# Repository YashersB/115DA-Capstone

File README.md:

# 115DA-Capstone
Github respitory for Pulse Oximeter

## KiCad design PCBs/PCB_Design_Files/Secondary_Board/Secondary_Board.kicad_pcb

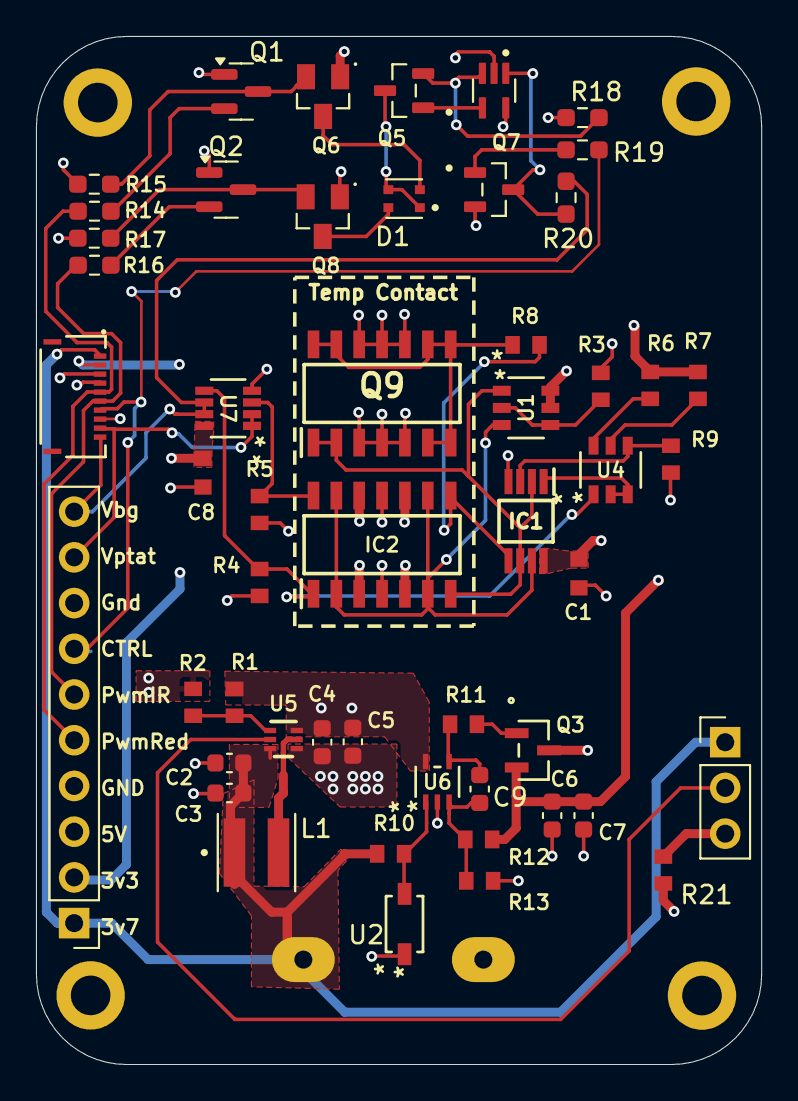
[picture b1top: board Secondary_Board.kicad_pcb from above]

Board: 4 copper layers, 40.3 x 57.1 mm, 57 parts (1 on the bottom side), 39 nets.

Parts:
BT2: Battery_Cell; bat_pads
C1, C8: .1u; 0603_capacitor
C2, C3, C6, C7: 4.7u; C_0603_1608Metric
C4, C5: 22u; C_0603_1608Metric
C9: 180p; C_0603_1608Metric
D1: VSMD66694; DIO_VSMD66694
H1, H2, H3, H4: MountingHole_Pad; MountingHole_2.2mm_M2_DIN965_Pad
IC1: TLV2333IDGKR
IC2: 320S14-U; That320_pnp
J1: 5034801000; Conn_FFC_10pin
J2: Conn_01x03_Pin; PinHeader_1x03_P2.54mm_Vertical
J4: Conn_01x10_Pin; PinHeader_1x10_P2.54mm_Vertical
L1: VSEB0430H-1R0MC; IND_VSEB0430H-1R0MC
Q1, Q2: MMBT3904; SOT-23
Q3: MMBT3904; SOT23_FAS
Q5, Q7: 2N7002
Q6, Q8: BSS84
Q9: 300S14-U; That300_npn
R1: 732k; 0603_resistor
R2, R21: 100k; 0603_resistor
R3: 40k; 0603_resistor
R4: 2.2k; 0603_resistor
R5: 5k; 0603_resistor
R6, R7: 1k; 0603_resistor
R8: 105; 0603_resistor
R9: 2050; 0603_resistor
R10: 250; 0603_resistor
R11: 100; 0603_resistor
R12: 3.96k; 0603_resistor
R13: 10k; 0603_resistor
R14, R19: 1k; R_0603_1608Metric_Pad0.98x0.95mm_HandSolder
R15, R17, R20: 10k; R_0603_1608Metric_Pad0.98x0.95mm_HandSolder
R16: R; R_0603_1608Metric_Pad0.98x0.95mm_HandSolder
R18: 60; R_0603_1608Metric_Pad0.98x0.95mm_HandSolder
U1, U4: DMMT5401-7-F; DMMT5401_Dual_PNP
U2: MMSZ5221BT1G; SOD-123_ONS
U5: TPS61023DRLR; DRL0006A
U6: TLV9101IDCKR; SC70-5_DCK_TEX
U7: TLV9002
U8: OPA333AIDCKR; OPA333

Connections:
+3.7V: BT2.1 (+), C2.1, C3.1, J1.1, J2.1, J4.1, L1.1, R10.1, U5.3 (VIN)
+3V3: C1.2, C6.1, C7.1, C8.2, IC1.8 (V+), IC2.3 (E1), IC2.5 (E3), IC2.10 (E4), IC2.12 (E2), J1.2, J4.2, Q3.2 (E), R6.1, R7.1, R12.2, U1.5 (E2), U1.6 (E1), U7.8 (V+)
+5V: C4.1, C5.1, J1.3, J4.3, Q3.3 (C), Q6.1 (G), Q8.1 (G), R1.1, R15.2, R17.2, U5.6 (VOUT), U6.5 (V+), U8.5 (V+)
/LED_Driver/Current Sink: D1.1, D1.3, Q5.3
/OP_CTRL: J1.7, J4.7, R19.2
/PTAT_Bandgap/Pnp_In+: IC1.5 (+IN_B), IC2.8 (C4), R8.1
/PTAT_Bandgap/Pnp_In-: IC1.2 (-IN_A), IC1.6 (-IN_B), IC2.7 (C3), Q9.1 (C1), Q9.2 (B1), U1.1 (C1)
/PTAT_Bandgap/Pnp_base: IC1.7 (OUT_B), IC2.2 (B1), IC2.6 (B3), IC2.9 (B4), IC2.13 (B2), U1.3 (B2)
/PTAT_Bandgap/Vbg: IC2.1 (C1), R4.1, U4.1 (C1), U7.5 (IN2+)
/PTAT_Bandgap/Vptat: IC2.14 (C2), R5.1, U7.3 (IN1+)
/PWM_IR: J1.6, J4.6, R16.1
/PWM_Red: J1.5, J4.5, R14.1
/Power Management/Vfb: R1.2, R2.1, U5.1 (FB)
/V_bandgap: J1.10, J4.10, R20.1, U7.6 (IN2-), U7.7 (OUT2)
/V_ptat: J1.9, J4.9, U7.1 (OUT1), U7.2 (IN1-)
GND: BT2.2 (-), C1.1, C2.2, C3.2, C4.2, C5.2, C6.2, C7.2, C8.1, H1.1, H2.1, H3.1, H4.1, IC1.4 (V-), IC2.4 (NC_1), IC2.11 (NC_2), J1.4, J1.8, J4.4, J4.8, Q1.1 (E), Q2.1 (E), Q7.2, Q9.3 (E1), Q9.4 (SUB_1), Q9.5 (E3), Q9.10 (E4), Q9.11 (SUB_2), Q9.12 (E2), R2.2, R3.2, R4.2, R5.2, R9.2, R13.1, R18.1, R21.2, U2.1 (CATHODE), U5.4 (GND), U6.2 (V-), U7.4 (V-), U8.2 (V-)
unnamed: IC1.3 (+IN_A), R9.1, U4.4 (C2)
unnamed: IC1.1 (OUT_A), U4.2 (B1), U4.3 (B2)
unnamed: J2.2, U5.2 (EN)
unnamed: J2.3, R21.1
unnamed: Q1.2 (B), R14.2
unnamed: Q1.3 (C), Q6.2 (S), R15.1
unnamed: Q2.2 (B), R16.2
unnamed: Q2.3 (C), Q8.2 (S), R17.1
unnamed: Q3.1 (B), R11.2
unnamed: D1.2, Q6.3 (D)
unnamed: Q7.1, R19.1
unnamed: D1.4, Q8.3 (D)
unnamed: Q9.6 (B3), Q9.7 (C3), Q9.8 (C4), Q9.9 (B4), Q9.13 (B2), Q9.14 (C2), R8.2
unnamed: R3.1, U1.2 (B1), U1.4 (C2)
unnamed: R10.2, U2.2 (ANODE), U6.1 (IN+)
unnamed: R6.2, U4.6 (E1)
unnamed: R7.2, U4.5 (E2)
unnamed: L1.2, U5.5 (SW)
unnamed: C9.2, R12.1, R13.2, U6.3 (IN-)
unnamed: C9.1, R11.1, U6.4 (OUT)
unnamed: Q7.3, R20.2, U8.1 (+IN)
unnamed: Q5.2, R18.2, U8.3 (-IN)
unnamed: Q5.1, U8.4 (OUT)

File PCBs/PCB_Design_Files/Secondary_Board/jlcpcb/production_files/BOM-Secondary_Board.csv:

Comment,Designator,Footprint,LCSC,Quantity
.1u,"C1,C8",0603_capacitor,C14663,2
100,R11,0603_resistor,C22775,1
100k,R2,0603_resistor,C25803,1
10k,"R13,R15,R17,R20",0603_resistor,C25804,4
1k,"R14,R19,R6,R7",R_0603_1608Metric_Pad0.98x0.95mm_HandSolder,C21190,4
2.2k,R4,0603_resistor,C4190,1
22u,"C4,C5",C_0603_1608Metric,C59461,2
2N7002,"Q5,Q7",2N7002,C8545,2
4.7u,"C2,C3,C6,C7",C_0603_1608Metric,C19666,4
5034801000,J1,Conn_FFC_10pin,C127355,1
MMBT3904,"Q1,Q2,Q3",SOT-23,C20526,3
TLV2333IDGKR,IC1,TLV2333IDGKR,C527573,1
VSMD66694,D1,DIO_VSMD66694,C511435,1
OPA333AIDCKR,U8,OPA333,,1
DMMT5401-7-F,U4,DMMT5401_Dual_PNP,,1
MMSZ5221BT1G,U2,SOD-123_ONS,,1
BSS84,Q6,BSS84,,1
250,R10,0603_resistor,,1
60,R18,R_0603_1608Metric_Pad0.98x0.95mm_HandSolder,,1
320S14-U,IC2,That320_pnp,,1
105,R8,0603_resistor,,1
3.96k,R12,0603_resistor,,1
VSEB0430H-1R0MC,L1,IND_VSEB0430H-1R0MC,,1
Conn_01x10_Pin,J4,PinHeader_1x10_P2.54mm_Vertical,,1
TPS61023DRLR,U5,DRL0006A,,1
180p,C9,C_0603_1608Metric,,1
732k,R1,0603_resistor,,1
5k,R5,0603_resistor,,1
TLV9002,U7,TLV9002,,1
300S14-U,Q9,That300_npn,,1
2050,R9,0603_resistor,,1
BSS84,Q8,BSS84,,1
40k,R3,0603_resistor,,1
TLV9101IDCKR,U6,SC70-5_DCK_TEX,,1
R,R16,R_0603_1608Metric_Pad0.98x0.95mm_HandSolder,,1
DMMT5401-7-F,U1,DMMT5401_Dual_PNP,,1
Battery_Cell,BT2,bat_pads,,1
100k,R21,0603_resistor,,1
Conn_01x03_Pin,J2,PinHeader_1x03_P2.54mm_Vertical,,1

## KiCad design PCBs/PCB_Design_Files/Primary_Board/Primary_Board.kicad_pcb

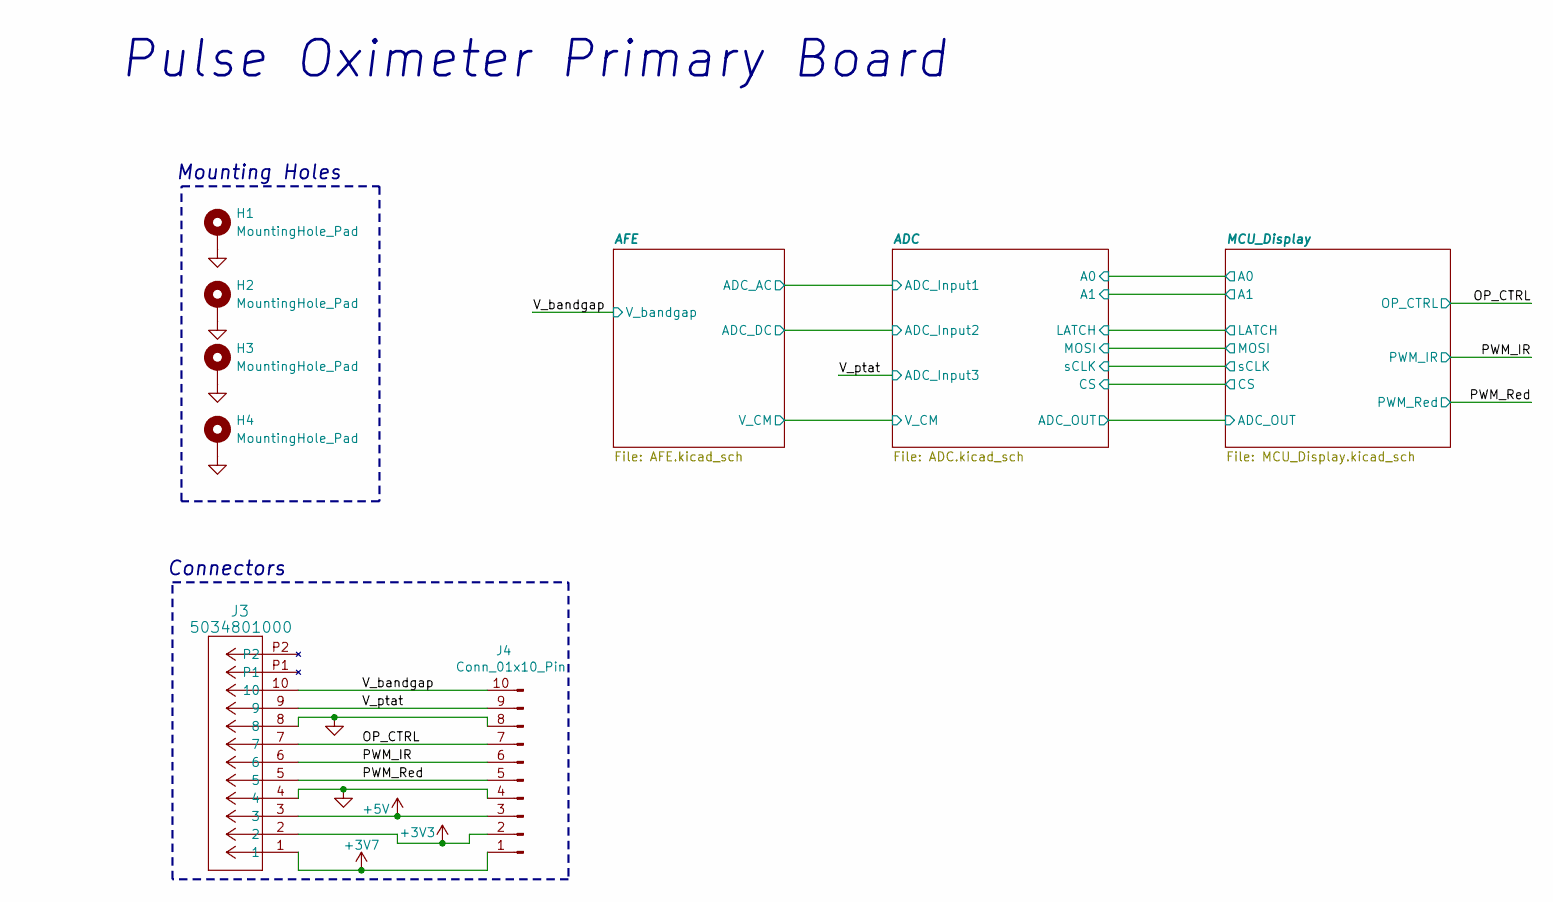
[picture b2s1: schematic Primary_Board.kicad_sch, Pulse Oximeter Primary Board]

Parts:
H1, H2, H3, H4: MountingHole_Pad; MountingHole_2.2mm_M2_DIN965_Pad
J3: 5034801000; Conn_FFC_10pin
J4: Conn_01x10_Pin; PinHeader_1x10_P2.54mm_Vertical

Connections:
+3V3: J3.2, J4.2; also elsewhere on the board
+3V7: J3.1, J4.1; also elsewhere on the board
+5V: J3.3, J4.3; also elsewhere on the board
/OP_CTRL: J3.7, J4.7; also elsewhere on the board
/PWM_IR: J3.6, J4.6; also elsewhere on the board
/PWM_Red: J3.5, J4.5; also elsewhere on the board
/V_bandgap: J3.10, J4.10; also elsewhere on the board
/V_ptat: J3.9, J4.9; also elsewhere on the board
GND: H1.1, H2.1, H3.1, H4.1, J3.4, J3.8, J4.4, J4.8; also elsewhere on the board

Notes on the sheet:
Mounting Holes
Pulse Oximeter Primary Board
Connectors

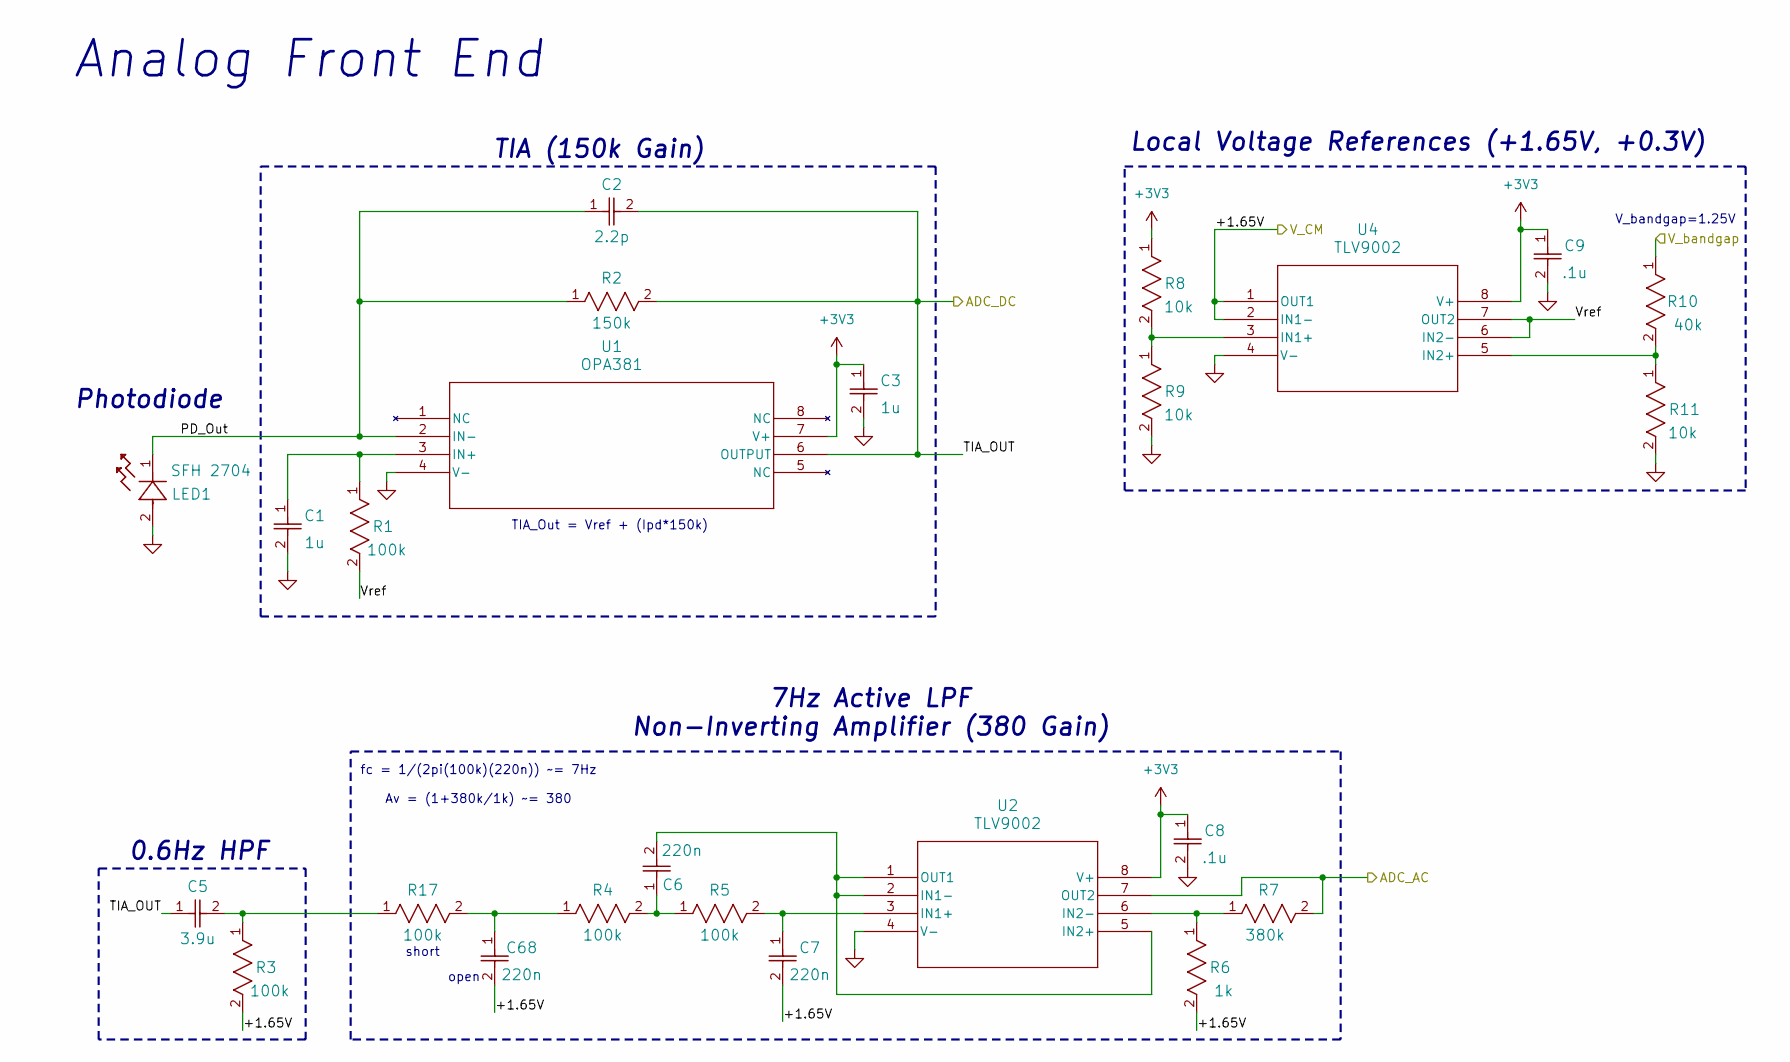
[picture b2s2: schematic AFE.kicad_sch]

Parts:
C1, C3: 1u; 0603_capacitor
C2: 2.2p; 0603_capacitor
C5: 3.9u; 0603_capacitor
C6, C7, C68: 220n; 0603_capacitor
C8, C9: .1u; 0603_capacitor
LED1: SFH 2704; SFH2704_LED
R1, R3, R4, R5, R17: 100k; 0603_resistor
R2: 150k; 0603_resistor
R6: 1k; 0603_resistor
R7: 380k; 0603_resistor
R8, R9, R11: 10k; 0603_resistor
R10: 40k; 0603_resistor
U1: OPA381
U2, U4: TLV9002

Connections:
+3V3: C3.1, C8.1, C9.1, R8.1, U1.7 (V+), U2.8 (V+), U4.8 (V+); also elsewhere on the board
/ADC/ADC_Input1: R7.2, U2.7 (OUT2); also elsewhere on the board
/AFE/+1.65V: C7.2, C68.2, R3.2, R6.2, U4.1 (OUT1), U4.2 (IN1-); also elsewhere on the board
/AFE/PD_Out: C2.1, LED1.1, R2.1, U1.2 (IN-)
/AFE/TIA_OUT: C2.2, C5.1, R2.2, U1.6 (OUTPUT); also elsewhere on the board
/AFE/Vref: R1.2, U4.6 (IN2-), U4.7 (OUT2)
/V_bandgap: R10.1; also elsewhere on the board
GND: C1.2, C3.2, C8.2, C9.2, LED1.2, R9.2, R11.2, U1.4 (V-), U2.4 (V-), U4.4 (V-); also elsewhere on the board
unnamed: C5.2, R3.1, R17.1
unnamed: C6.1, R4.2, R5.1
unnamed: C68.1, R4.1, R17.2
unnamed: C1.1, R1.1, U1.3 (IN+)
unnamed: C7.1, R5.2, U2.3 (IN1+)
unnamed: C6.2, U2.1 (OUT1), U2.2 (IN1-), U2.5 (IN2+)
unnamed: R6.1, R7.1, U2.6 (IN2-)
unnamed: R8.2, R9.1, U4.3 (IN1+)
unnamed: R10.2, R11.1, U4.5 (IN2+)

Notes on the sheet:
V_bandgap=1.25V
Local Voltage References (+1.65V, +0.3V)
Analog Front End
TIA_Out = Vref + (Ipd*150k)
TIA (150k Gain)
Photodiode
0.6Hz HPF
short
7Hz Active LPF Non-Inverting Amplifier (380 Gain)
open
fc = 1/(2pi(100k)(220n)) ~= 7Hz Av = (1+380k/1k) ~= 380

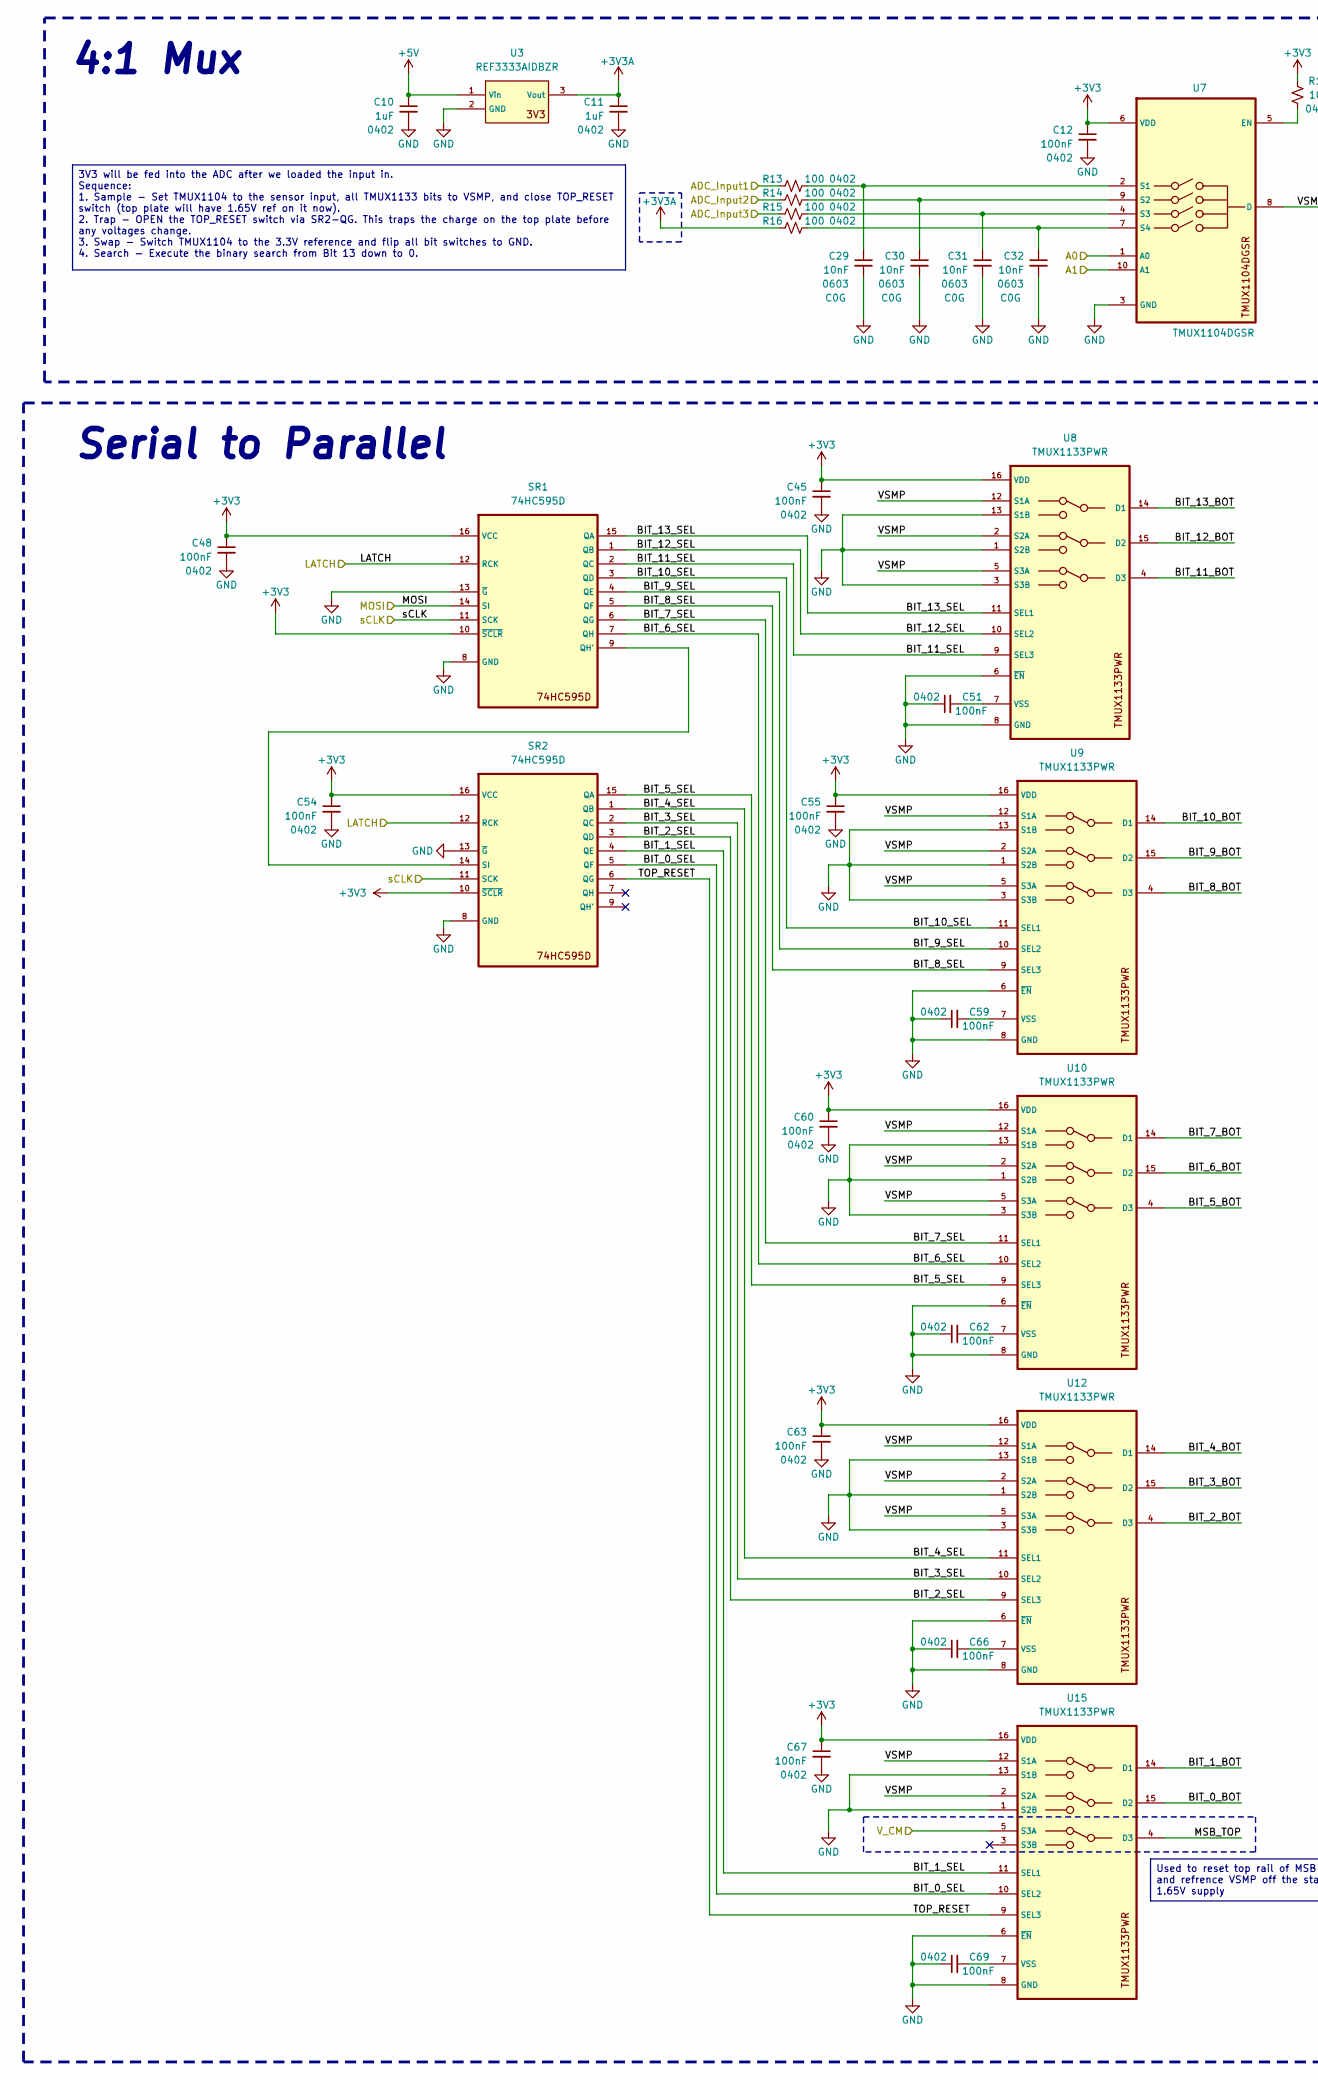
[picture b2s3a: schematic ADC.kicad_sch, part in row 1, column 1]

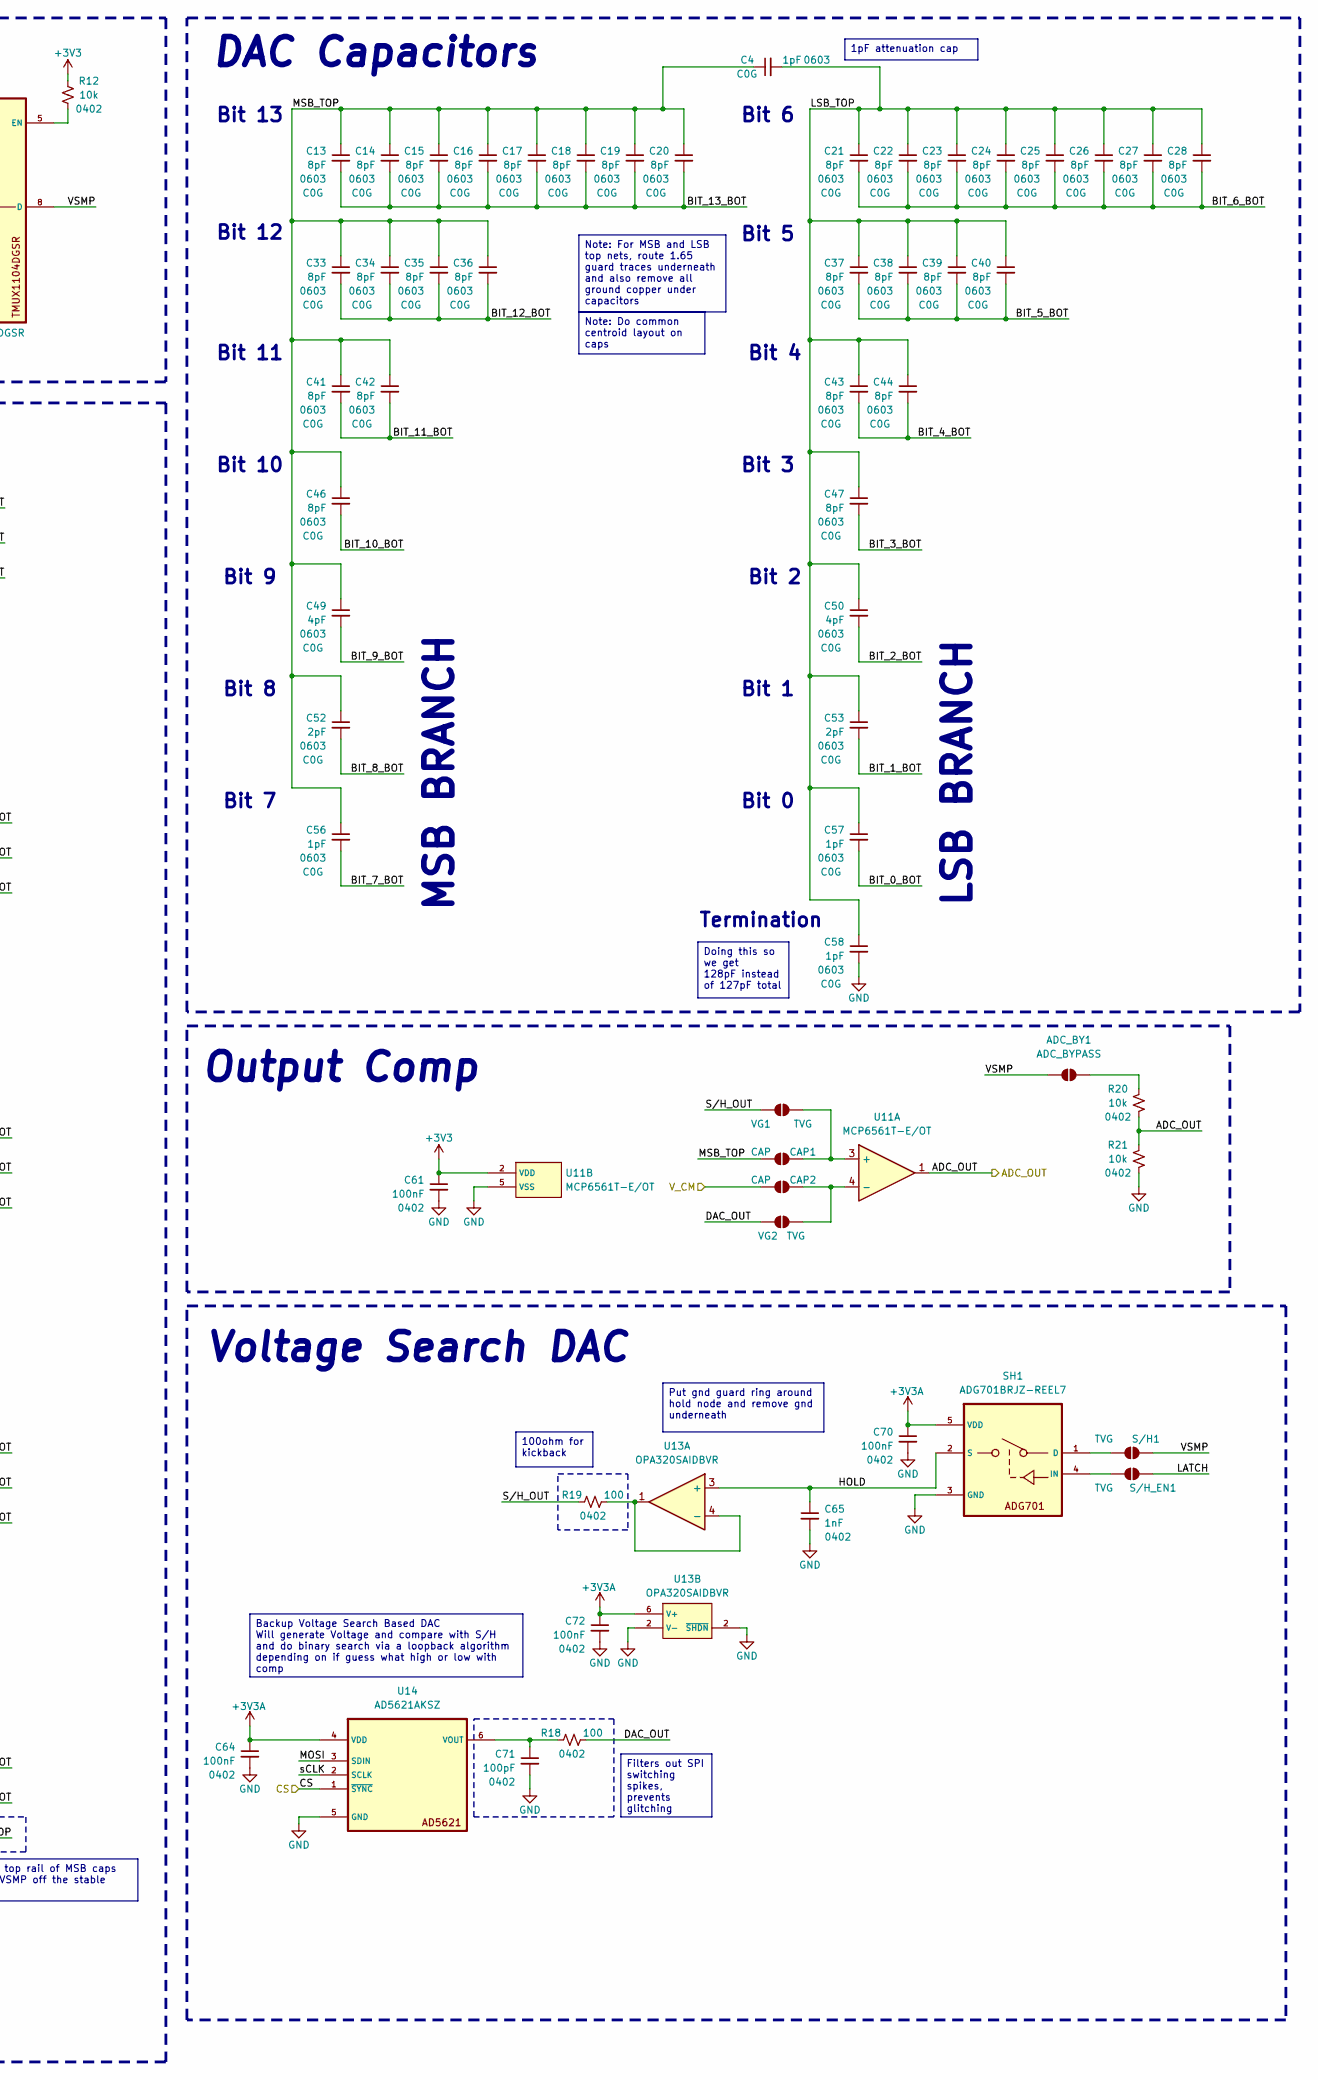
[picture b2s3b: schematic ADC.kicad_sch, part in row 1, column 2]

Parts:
ADC_BY1: ADC_BYPASS; SolderJumper-2_P1.3mm_Open_Pad1.0x1.5mm
C4, C56, C57, C58: 1pF; C_0603_1608Metric
C10, C11: 1uF; C_0402_1005Metric
C12, C45, C48, C51, C54, C55, C59, C60, C61, C62, C63, C64, C66, C67, C69, C70, C72: 100nF; C_0402_1005Metric
C13, C14, C15, C16, C17, C18, C19, C20, C21, C22, C23, C24, C25, C26, C27, C28, C33, C34, C35, C36, C37, C38, C39, C40, C41, C42, C43, C44, C46, C47: 8pF; C_0603_1608Metric
C29, C30, C31, C32: 10nF; C_0603_1608Metric
C49, C50: 4pF; C_0603_1608Metric
C52, C53: 2pF; C_0603_1608Metric
C65: 1nF; C_0402_1005Metric
C71: 100pF; C_0402_1005Metric
CAP1, CAP2: CAP; SolderJumper-2_P1.3mm_Open_Pad1.0x1.5mm
R12, R20, R21: 10k; R_0402_1005Metric
R13, R14, R15, R16, R18, R19: 100; R_0402_1005Metric
S/H1: TVG; SolderJumper-2_P1.3mm_Open_Pad1.0x1.5mm
S/H_EN1: TVG; SolderJumper-2_P1.3mm_Open_Pad1.0x1.5mm
SH1: ADG701BRJZ-REEL7; SOT-23-5_HandSoldering
SR1, SR2: 74HC595D; SOIC-16_3.9x9.9mm_P1.27mm
U3: REF3333AIDBZR; SOT-23-3
U7: TMUX1104DGSR; VSSOP-10_3x3mm_P0.5mm
U8, U9, U10, U12, U15: TMUX1133PWR; TSSOP-16_4.4x5mm_P0.65mm
U11: MCP6561T-E/OT; SOT-23-5_HandSoldering
U13: OPA320SAIDBVR; SOT-23-6_Handsoldering
U14: AD5621AKSZ; SOT-363_SC-70-6
VG1, VG2: TVG; SolderJumper-2_P1.3mm_Open_Pad1.0x1.5mm

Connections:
+3V3: C12.1, C45.1, C48.1, C54.1, C55.1, C60.1, C61.1, C63.1, C67.1, R12.2, SR1.10 (~SCLR), SR1.16 (VCC), SR2.10 (~SCLR), SR2.16 (VCC), U7.6 (VDD), U8.16 (VDD), U9.16 (VDD), U10.16 (VDD), U11.2 (VDD), U12.16 (VDD), U15.16 (VDD); also elsewhere on the board
+3V3A: C11.1, C64.1, C70.1, C72.1, R16.1, SH1.5 (VDD), U3.3 (Vout), U13.6 (V+), U14.4 (VDD)
+5V: C10.1, U3.1 (Vin); also elsewhere on the board
/ADC/A0: U7.1 (A0); also elsewhere on the board
/ADC/A1: U7.10 (A1); also elsewhere on the board
/ADC/ADC_Input1: R13.1; also elsewhere on the board
/ADC/ADC_OUT: R20.1, R21.2, U11.1; also elsewhere on the board
/ADC/BIT_0_BOT: C57.2, U15.15 (D2)
/ADC/BIT_0_SEL: SR2.5 (QF), U15.10 (SEL2)
/ADC/BIT_1_BOT: C53.2, U15.14 (D1)
/ADC/BIT_1_SEL: SR2.4 (QE), U15.11 (SEL1)
/ADC/BIT_2_BOT: C50.2, U12.4 (D3)
/ADC/BIT_2_SEL: SR2.3 (QD), U12.9 (SEL3)
/ADC/BIT_3_BOT: C47.2, U12.15 (D2)
/ADC/BIT_3_SEL: SR2.2 (QC), U12.10 (SEL2)
/ADC/BIT_4_BOT: C43.2, C44.2, U12.14 (D1)
/ADC/BIT_4_SEL: SR2.1 (QB), U12.11 (SEL1)
/ADC/BIT_5_BOT: C37.2, C38.2, C39.2, C40.2, U10.4 (D3)
/ADC/BIT_5_SEL: SR2.15 (QA), U10.9 (SEL3)
/ADC/BIT_6_BOT: C21.2, C22.2, C23.2, C24.2, C25.2, C26.2, C27.2, C28.2, U10.15 (D2)
/ADC/BIT_6_SEL: SR1.7 (QH), U10.10 (SEL2)
/ADC/BIT_7_BOT: C56.2, U10.14 (D1)
/ADC/BIT_7_SEL: SR1.6 (QG), U10.11 (SEL1)
/ADC/BIT_8_BOT: C52.2, U9.4 (D3)
/ADC/BIT_8_SEL: SR1.5 (QF), U9.9 (SEL3)
/ADC/BIT_9_BOT: C49.2, U9.15 (D2)
/ADC/BIT_9_SEL: SR1.4 (QE), U9.10 (SEL2)
/ADC/BIT_10_BOT: C46.2, U9.14 (D1)
/ADC/BIT_10_SEL: SR1.3 (QD), U9.11 (SEL1)
/ADC/BIT_11_BOT: C41.2, C42.2, U8.4 (D3)
/ADC/BIT_11_SEL: SR1.2 (QC), U8.9 (SEL3)
/ADC/BIT_12_BOT: C33.2, C34.2, C35.2, C36.2, U8.15 (D2)
/ADC/BIT_12_SEL: SR1.1 (QB), U8.10 (SEL2)
/ADC/BIT_13_BOT: C13.2, C14.2, C15.2, C16.2, C17.2, C18.2, C19.2, C20.2, U8.14 (D1)
/ADC/BIT_13_SEL: SR1.15 (QA), U8.11 (SEL1)
/ADC/CS: U14.1 (~SYNC); also elsewhere on the board
/ADC/DAC_OUT: R18.2, VG2.1 (A)
/ADC/HOLD: C65.1, SH1.2 (S), U13.3 (+)
/ADC/LATCH: S/H_EN1.1 (A), SR1.12 (RCK), SR2.12 (RCK); also elsewhere on the board
/ADC/LSB_TOP: C4.2, C21.1, C22.1, C23.1, C24.1, C25.1, C26.1, C27.1, C28.1, C37.1, C38.1, C39.1, C40.1, C43.1, C44.1, C47.1, C50.1, C53.1, C57.1, C58.1
/ADC/MOSI: SR1.14 (SI), U14.3 (SDIN); also elsewhere on the board
/ADC/MSB_TOP: C4.1, C13.1, C14.1, C15.1, C16.1, C17.1, C18.1, C19.1, C20.1, C33.1, C34.1, C35.1, C36.1, C41.1, C42.1, C46.1, C49.1, C52.1, C56.1, CAP1.1 (A), U15.4 (D3)
/ADC/S/H_OUT: R19.1, VG1.1 (A)
/ADC/TOP_RESET: SR2.6 (QG), U15.9 (SEL3)
/ADC/VSMP: ADC_BY1.1 (A), S/H1.1 (A), U7.8 (D), U8.2 (S2A), U8.5 (S3A), U8.12 (S1A), U9.2 (S2A), U9.5 (S3A), U9.12 (S1A), U10.2 (S2A), U10.5 (S3A), U10.12 (S1A), U12.2 (S2A), U12.5 (S3A), U12.12 (S1A), U15.2 (S2A), U15.12 (S1A)
/ADC/sCLK: SR1.11 (SCK), SR2.11 (SCK), U14.2 (SCLK); also elsewhere on the board
/AFE/+1.65V: CAP2.1 (A), U15.5 (S3A); also elsewhere on the board
/AFE/TIA_OUT: R14.1; also elsewhere on the board
/V_ptat: R15.1; also elsewhere on the board
GND: C10.2, C11.2, C12.2, C29.2, C30.2, C31.2, C32.2, C45.2, C48.2, C51.1, C54.2, C55.2, C58.2, C59.1, C60.2, C61.2, C62.1, C63.2, C64.2, C65.2, C66.1, C67.2, C69.1, C70.2, C71.2, C72.2, R21.1, SH1.3 (GND), SR1.8 (GND), SR1.13 (~G), SR2.8 (GND), SR2.13 (~G), U3.2 (GND), U7.3 (GND), U8.1 (S2B), U8.3 (S3B), U8.6 (~EN), U8.8 (GND), U8.13 (S1B), U9.1 (S2B), U9.3 (S3B), U9.6 (~EN), U9.8 (GND), U9.13 (S1B), U10.1 (S2B), U10.3 (S3B), U10.6 (~EN), U10.8 (GND), U10.13 (S1B), U11.5 (VSS), U12.1 (S2B), U12.3 (S3B), U12.6 (~EN), U12.8 (GND), U12.13 (S1B), U13.2 (V-), U14.5 (GND), U15.1 (S2B), U15.6 (~EN), U15.8 (GND), U15.13 (S1B); also elsewhere on the board
unnamed: ADC_BY1.2 (B), R20.2
unnamed: CAP1.2 (B), U11.3 (+), VG1.2 (B)
unnamed: CAP2.2 (B), U11.4 (-), VG2.2 (B)
unnamed: S/H1.2 (B), SH1.1 (D)
unnamed: S/H_EN1.2 (B), SH1.4 (IN)
unnamed: SR1.9 (QH'), SR2.14 (SI)
unnamed: R12.1, U7.5 (EN)
unnamed: C29.1, R13.2, U7.2 (S1)
unnamed: C30.1, R14.2, U7.9 (S2)
unnamed: C31.1, R15.2, U7.4 (S3)
unnamed: C32.1, R16.2, U7.7 (S4)
unnamed: C51.2, U8.7 (VSS)
unnamed: C59.2, U9.7 (VSS)
unnamed: C62.2, U10.7 (VSS)
unnamed: C66.2, U12.7 (VSS)
unnamed: R19.2, U13.1, U13.4 (-)
unnamed: C71.1, R18.1, U14.6 (VOUT)
unnamed: C69.2, U15.7 (VSS)

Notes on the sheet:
Bit 13
Termination
Bit 2
Bit 3
Bit 10
Bit 9
Bit 6
LSB BRANCH
Bit 1
Serial to Parallel
Bit 12
MSB BRANCH
4:1 Mux
Bit 7
Bit 8
Voltage Search DAC
Bit 0
Bit 4
Bit 5
Output Comp
Bit 11
DAC Capacitors
Filters out SPI switching spikes, prevents glitching
1pF attenuation cap
Note: Do common centroid layout on caps
Put gnd guard ring around hold node and remove gnd underneath
Used to reset top rail of MSB caps and refrence VSMP off the stable 1.65V supply
Doing this so we get 128pF instead of 127pF total
Note: For MSB and LSB top nets, route 1.65 guard traces underneath and also remove all ground copper under capacitors
3V3 will be fed into the ADC after we loaded the input in. Sequence: 1. Sample - Set TMUX1104 to the sensor input, all TMUX1133 bits to VSMP, and close TOP_RESET switch (top plate will have 1.65V ref on it now). 2. Trap - OPEN the TOP_RESET switch via SR2-QG. This traps the charge on the top plate 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
Backup Voltage Search Based DAC Will generate Voltage and compare with S/H and do binary search via a loopback algorithm depending on if guess what high or low with comp
100ohm for kickback

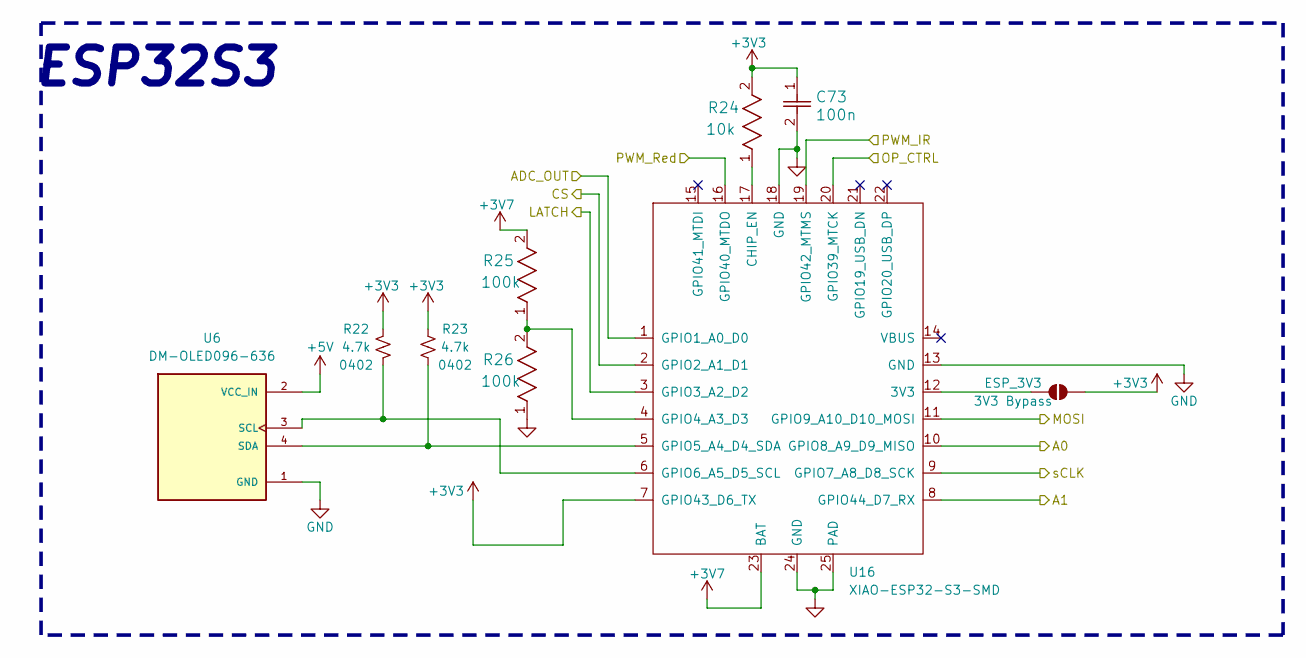
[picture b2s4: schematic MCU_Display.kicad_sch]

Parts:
C73: 100n; 0603_capacitor
ESP_3V3: 3V3 Bypass; SolderJumper-2_P1.3mm_Open_Pad1.0x1.5mm
R22, R23: 4.7k; R_0402_1005Metric
R24: 10k; 0603_resistor
R25, R26: 100k; 0603_resistor
U6: DM-OLED096-636; OLED096-636
U16: XIAO-ESP32-S3-SMD

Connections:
+3V3: C73.1, ESP_3V3.2 (B), R22.2, R23.2, R24.2, U16.7 (GPIO43_D6_TX); also elsewhere on the board
+3V7: R25.2, U16.23 (BAT); also elsewhere on the board
+5V: U6.2 (VCC_IN); also elsewhere on the board
/ADC/A0: U16.10 (GPIO8_A9_D9_MISO); also elsewhere on the board
/ADC/A1: U16.8 (GPIO44_D7_RX); also elsewhere on the board
/ADC/ADC_OUT: U16.1 (GPIO1_A0_D0); also elsewhere on the board
/ADC/CS: U16.2 (GPIO2_A1_D1); also elsewhere on the board
/ADC/LATCH: U16.3 (GPIO3_A2_D2); also elsewhere on the board
/ADC/MOSI: U16.11 (GPIO9_A10_D10_MOSI); also elsewhere on the board
/ADC/sCLK: U16.9 (GPIO7_A8_D8_SCK); also elsewhere on the board
/OP_CTRL: U16.20 (GPIO39_MTCK); also elsewhere on the board
/PWM_IR: U16.19 (GPIO42_MTMS); also elsewhere on the board
/PWM_Red: U16.16 (GPIO40_MTDO); also elsewhere on the board
GND: C73.2, R26.1, U6.1 (GND), U16.13 (GND), U16.18 (GND), U16.24 (GND), U16.25 (PAD); also elsewhere on the board
unnamed: ESP_3V3.1 (A), U16.12 (3V3)
unnamed: R24.1, U16.17 (CHIP_EN)
unnamed: R25.1, R26.2, U16.4 (GPIO4_A3_D3)
unnamed: R23.1, U6.4 (SDA), U16.5 (GPIO5_A4_D4_SDA)
unnamed: R22.1, U6.3 (SCL), U16.6 (GPIO6_A5_D5_SCL)

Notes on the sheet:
ESP32S3

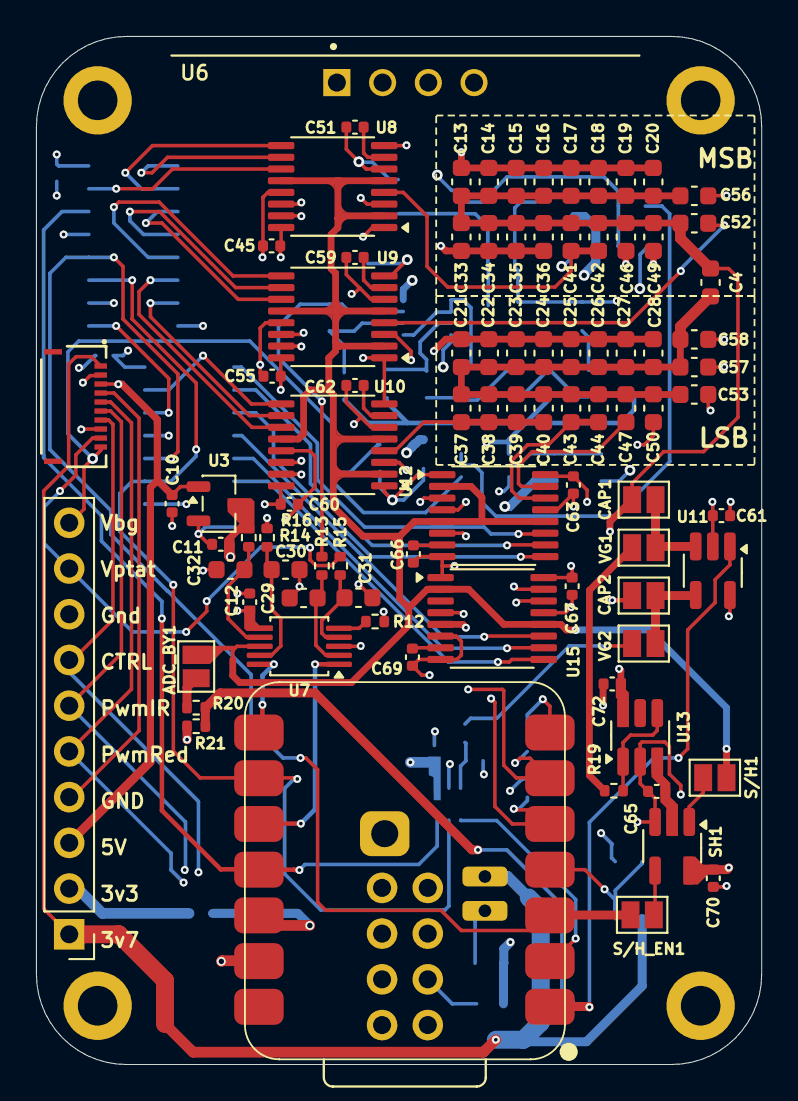
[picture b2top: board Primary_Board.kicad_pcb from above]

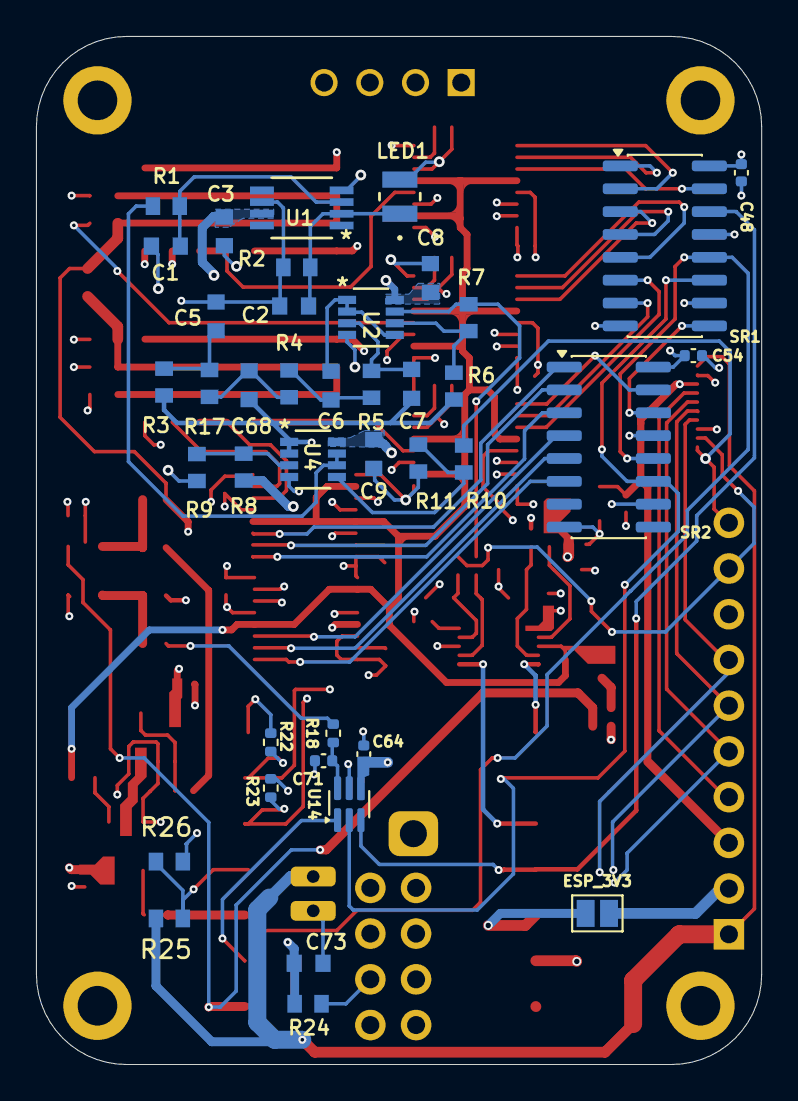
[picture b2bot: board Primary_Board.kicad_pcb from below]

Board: 4 copper layers, 40.3 x 57.1 mm, 132 parts (40 on the bottom side), 89 nets.

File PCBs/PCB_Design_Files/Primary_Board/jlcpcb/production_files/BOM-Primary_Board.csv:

Comment,Designator,Footprint,LCSC,Quantity
.1u,"C8,C9",0603_capacitor,C14663,2
100,"R13,R14,R15,R16,R18,R19",R_0402_1005Metric,C25076,6
100k,"R1,R17,R3,R4,R5",0603_resistor,C25803,5
100nF,"C12,C45,C48,C51,C54,C55,C59,C60,C61,C62,C63,C64,C66,C67,C69,C70,C72",C_0402_1005Metric,C1525,17
100pF,C71,C_0402_1005Metric,C1546,1
10k,"R12,R20,R21",R_0402_1005Metric,C25744,3
10k,"R11,R24,R8,R9",0603_resistor,C25804,4
10nF,"C29,C30,C31,C32",C_0603_1608Metric,C3836718,4
150k,R2,0603_resistor,C22807,1
1k,R6,0603_resistor,C21190,1
1nF,C65,C_0402_1005Metric,C1523,1
1pF,"C4,C56,C57,C58",C_0603_1608Metric,C2181373,4
1u,"C1,C3",0603_capacitor,C15849,2
1uF,"C10,C11",C_0402_1005Metric,C52923,2
220n,"C6,C68,C7",0603_capacitor,C21120,3
2pF,"C52,C53",C_0603_1608Metric,C513620,2
4.7k,"R22,R23",R_0402_1005Metric,C25900,2
4pF,"C49,C50",C_0603_1608Metric,C309461,2
5034801000,J3,Conn_FFC_10pin,C127355,1
74HC595D,"SR1,SR2",SOIC-16_3.9x9.9mm_P1.27mm,C5947,2
8pF,"C13,C14,C15,C16,C17,C18,C19,C20,C21,C22,C23,C24,C25,C26,C27,C28,C33,C34,C35,C36,C37,C38,C39,C40,C41,C42,C43,C44,C46,C47",C_0603_1608Metric,C519117,30
AD5621AKSZ,U14,SOT-363_SC-70-6,C114054,1
ADG701BRJZ-REEL7,SH1,SOT-23-5_HandSoldering,C657566,1
OPA320SAIDBVR,U13,SOT-23-6_Handsoldering,C2057613,1
OPA381,U1,OPA381,C2870973,1
REF3333AIDBZR,U3,SOT-23-3,C130016,1
SFH 2704,LED1,SFH2704_LED,C2833005,1
TLV9002,"U2,U4",TLV9002,C2862620,2
TMUX1104DGSR,U7,VSSOP-10_3x3mm_P0.5mm,C2879206,1
TMUX1133PWR,"U10,U12,U15,U8,U9",TSSOP-16_4.4x5mm_P0.65mm,C1849385,5
DM-OLED096-636,U6,OLED096-636,,1
MCP6561T-E/OT,U11,SOT-23-5_HandSoldering,,1
40k,R10,0603_resistor,,1
2.2p,C2,0603_capacitor,,1
380k,R7,0603_resistor,,1
3.9u,C5,0603_capacitor,,1
Conn_01x10_Pin,J4,PinHeader_1x10_P2.54mm_Vertical,,1
XIAO-ESP32-S3-SMD,U16,XIAO-ESP32-S3-SMD,,1
100n,C73,0603_capacitor,,1
100k,R25,0603_resistor,,1
100k,R26,0603_resistor,,1
